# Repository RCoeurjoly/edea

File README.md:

# edea python library

The core python library and command line interface for the EDeA project.

## Documentation
[latest docs](https://edea-dev.gitlab.io/edea/latest/)

## Getting started
[Getting started](https://edea-dev.gitlab.io/edea/latest/get_started.html)

## CHANGELOG
[CHANGELOG](https://edea-dev.gitlab.io/edea/latest/changelog.html)

## Developer documentation
[Developer docs](https://edea-dev.gitlab.io/edea/latest/developer.html)

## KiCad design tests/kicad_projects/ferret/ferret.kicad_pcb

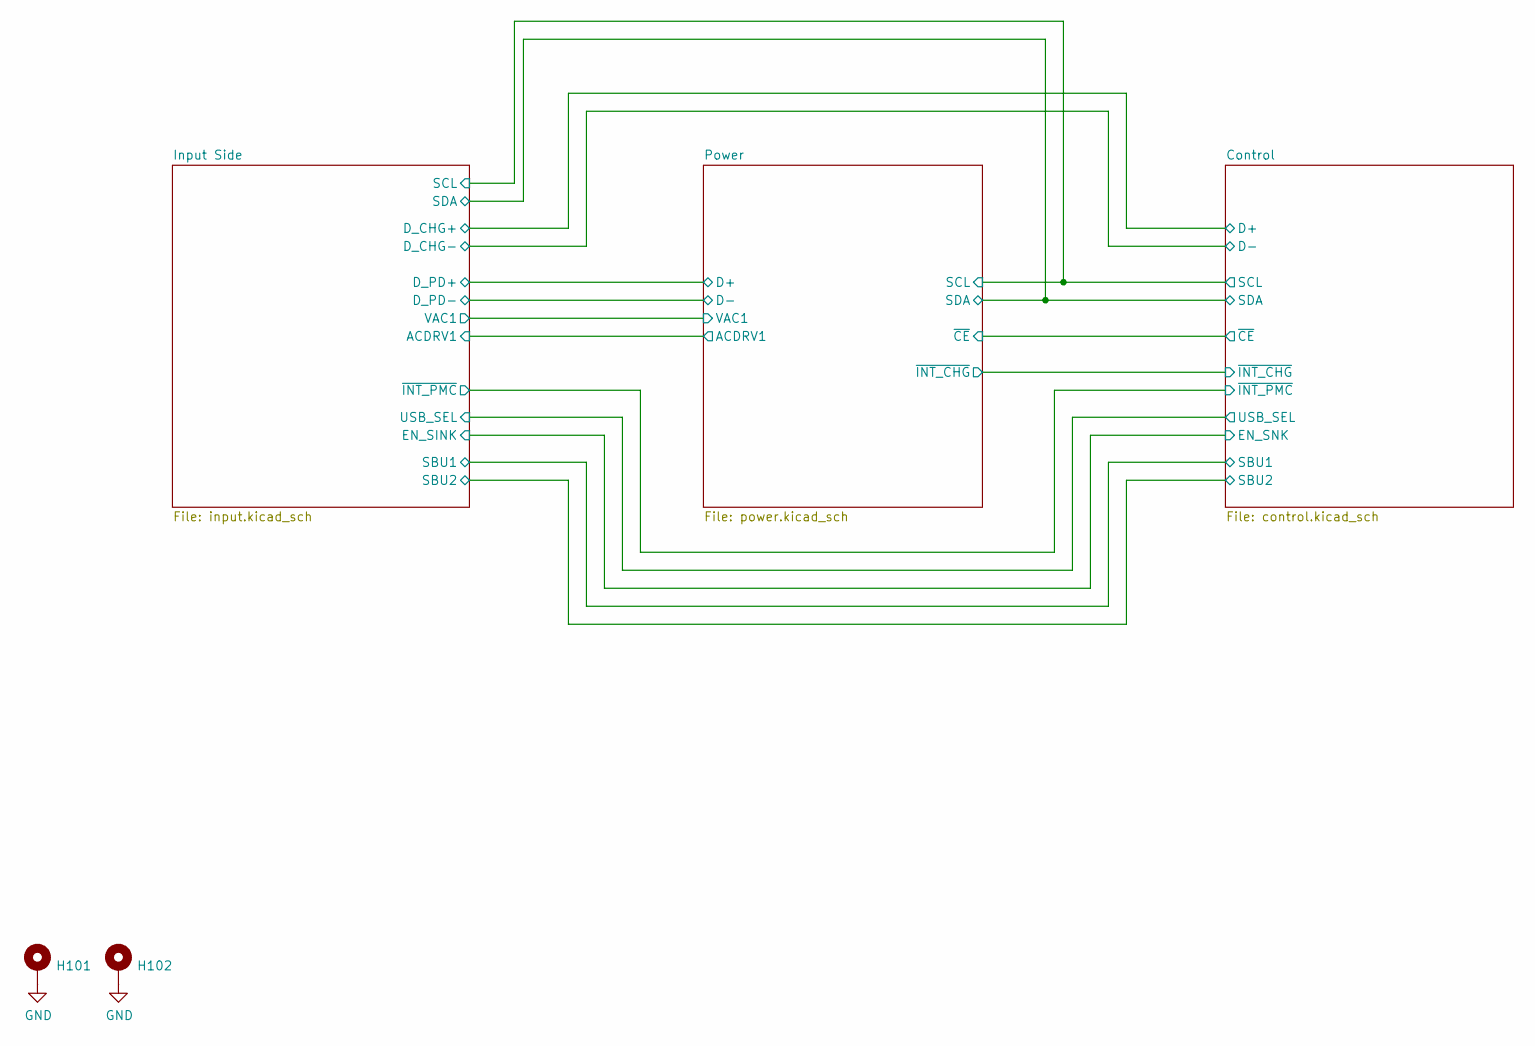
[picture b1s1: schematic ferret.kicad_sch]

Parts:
H101, H102: MountingHole_Pad; MountingHole_3.2mm_M3_ISO14580_Pad; MPN DNP

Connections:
GND: H101.1, H102.1; also elsewhere on the board

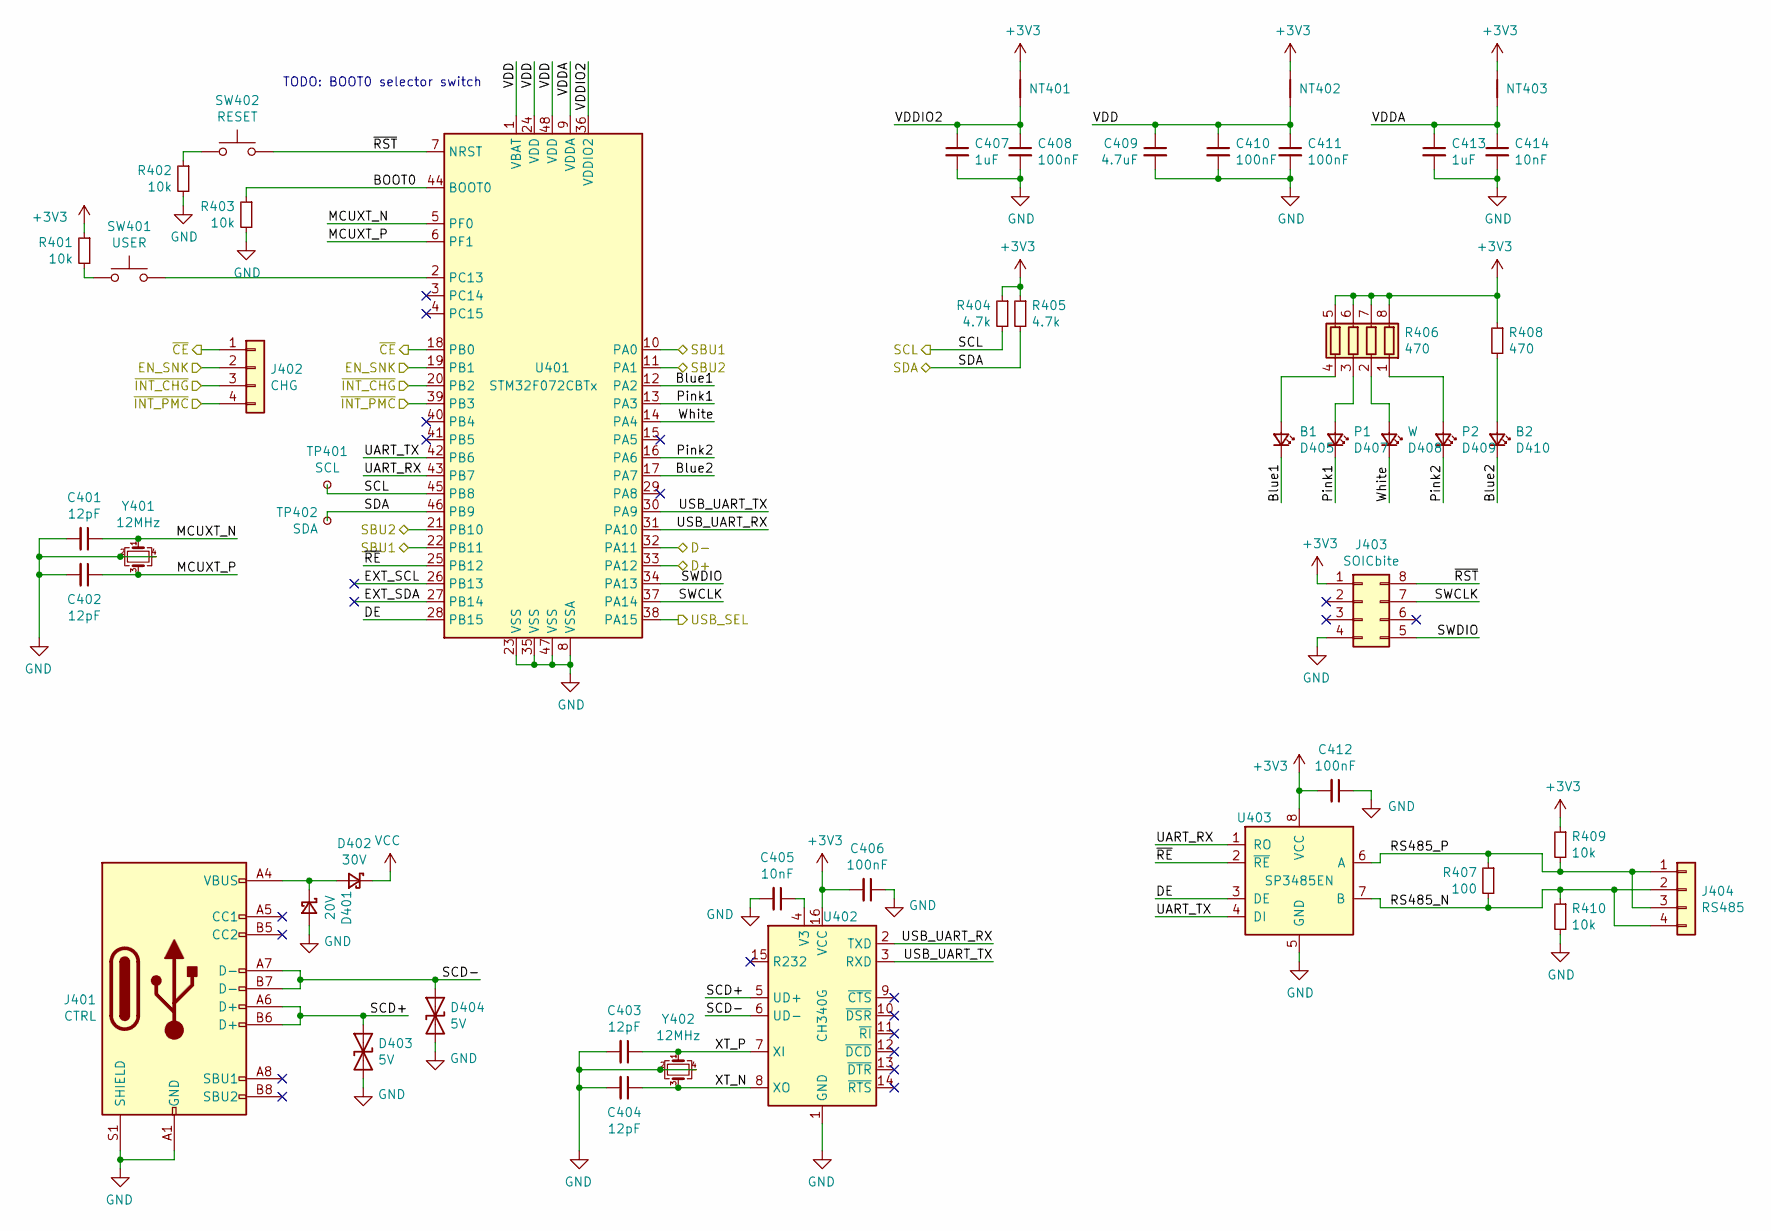
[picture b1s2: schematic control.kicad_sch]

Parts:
C401, C402, C403, C404: 12pF; C_0402_1005Metric; MPN 0402CG120J500NT; LCSC C1547
C405, C414: 10nF; C_0402_1005Metric; LCSC C15195
C406, C408, C410, C411, C412: 100nF; C_0402_1005Metric; MPN CL05B104KO5NNNC; JLC 0402
C407, C413: 1uF; C_0402_1005Metric; LCSC C52923
C409: 4.7uF; C_0603_1608Metric; MPN CL10A475KO8NNNC; JLC 0603
D401: 20V; D_SOD-123; MPN B5819W; LCSC C8598
D402: 30V; D_SOD-123; MPN B5819W; LCSC C8598
D403, D404: 5V; D_SOD-523; MPN ESD5Z3.3T1G; JLC SOD-523
D405: B1; LED_0603_1608Metric_Castellated; MPN OSB60603C1E
D407: P1; LED_0603_1608Metric_Castellated; MPN OSK40603C1E
D408: W; LED_0603_1608Metric_Castellated; MPN OSW50603C1E
D409: P2; LED_0603_1608Metric_Castellated; MPN OSK40603C1E
D410: B2; LED_0603_1608Metric_Castellated; MPN OSB60603C1E
J401: CTRL; USB_C_Receptacle_XKB_U262-16XN-4BVC11
J402: CHG; PinHeader_1x04_P2.54mm_Vertical
J403: SOICbite; SOIC_clipProgSmall
J404: RS485; PinHeader_1x04_P2.54mm_Vertical
NT401: VDDIO2; NetTie-2_SMD_Pad0.5mm; MPN DNP
NT402: VDD; NetTie-2_SMD_Pad0.5mm; MPN DNP
NT403: VDDA; NetTie-2_SMD_Pad0.5mm; MPN DNP
R401, R402, R403, R409, R410: 10k; R_0603_1608Metric; JLC 0603
R404, R405: 4.7k; R_0603_1608Metric; JLC 0603
R406: 470; R_Array_Convex_4x0603; MPN 4D03WGJ0471T5E; JLC 0603_x4
R407: 100; R_0603_1608Metric; MPN 0603WAF1000T5E; JLC 0603
R408: 470; R_0603_1608Metric; JLC 0603
SW401: USER; SW_SPST_PTS636_G
SW402: RESET; SW_SPST_PTS636_G
TP401: SCL; TestPoint_THTPad_D2.0mm_Drill1.0mm
TP402: SDA; TestPoint_THTPad_D2.0mm_Drill1.0mm
U401: STM32F072CBTx; LQFP-48_7x7mm_P0.5mm; MPN STM32F072C8T6; JLC LQFP-48_7.0x7.0x0.5P
U402: CH340G; SOIC-16_3.9x9.9mm_P1.27mm; MPN CH340G; JLC SOIC-16_3.9x9.9x1.27P
U403: SP3485EN; SOIC-8_3.9x4.9mm_P1.27mm; MPN SP3485EN-L/TR; JLC SOIC-8_3.9x4.9x1.27P
Y401, Y402: 12MHz; Crystal_SMD_3225-4Pin_3.2x2.5mm; MPN X322512MSB4SI; JLC SMD-3225_4P

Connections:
+3V3: C406.2, C412.2, J403.1, NT401.1, NT402.1, NT403.1, R401.1, R404.1, R405.1, R406.5 (R4.2), R406.6 (R3.2), R406.7 (R2.2), R406.8 (R1.2), R408.1, R409.1, U402.16 (VCC), U403.8 (VCC); also elsewhere on the board
/Control/BOOT0: R403.1, U401.44 (BOOT0)
/Control/Blue1: D405.1 (K), U401.12 (PA2)
/Control/Blue2: D410.1 (K), U401.17 (PA7)
/Control/D+: U401.33 (PA12); also elsewhere on the board
/Control/D-: U401.32 (PA11); also elsewhere on the board
/Control/DE: U401.28 (PB15), U403.3 (DE)
/Control/EXT_SCL: U401.26 (PB13)
/Control/EXT_SDA: U401.27 (PB14)
/Control/MCUXT_N: C401.1, U401.5 (PF0), Y401.1
/Control/MCUXT_P: C402.1, U401.6 (PF1), Y401.3
/Control/Pink1: D407.1 (K), U401.13 (PA3)
/Control/Pink2: D409.1 (K), U401.16 (PA6)
/Control/RS485_N: J404.2, J404.4, R407.2, R410.1, U403.7 (B)
/Control/RS485_P: J404.1, J404.3, R407.1, R409.2, U403.6 (A)
/Control/SBU1: U401.10 (PA0), U401.22 (PB11); also elsewhere on the board
/Control/SBU2: U401.11 (PA1), U401.21 (PB10); also elsewhere on the board
/Control/SCD+: D403.1 (A1), J401.A6 (D+), J401.B6 (D+), U402.5 (UD+)
/Control/SCD-: D404.1 (A1), J401.A7 (D-), J401.B7 (D-), U402.6 (UD-)
/Control/SCL: R404.2, TP401.1, U401.45 (PB8); also elsewhere on the board
/Control/SDA: R405.2, TP402.1, U401.46 (PB9); also elsewhere on the board
/Control/SWCLK: J403.7, U401.37 (PA14)
/Control/SWDIO: J403.5, U401.34 (PA13)
/Control/UART_RX: U401.43 (PB7), U403.1 (RO)
/Control/UART_TX: U401.42 (PB6), U403.4 (DI)
/Control/USB_SEL: U401.38 (PA15); also elsewhere on the board
/Control/USB_UART_RX: U401.31 (PA10), U402.2 (TXD)
/Control/USB_UART_TX: U401.30 (PA9), U402.3 (RXD)
/Control/VDD: C409.1, C410.1, C411.1, NT402.2, U401.1 (VBAT), U401.24 (VDD), U401.48 (VDD)
/Control/VDDA: C413.1, C414.1, NT403.2, U401.9 (VDDA)
/Control/VDDIO2: C407.1, C408.1, NT401.2, U401.36 (VDDIO2)
/Control/White: D408.1 (K), U401.14 (PA4)
/Control/XT_N: C404.1, U402.8 (XO), Y402.3
/Control/XT_P: C403.1, U402.7 (XI), Y402.1
/Control/~CE: J402.1, U401.18 (PB0); also elsewhere on the board
/Control/~INT_CHG: J402.3, U401.20 (PB2); also elsewhere on the board
/Control/~INT_PMC: J402.4, U401.39 (PB3); also elsewhere on the board
/Control/~RE: U401.25 (PB12), U403.2 (~RE)
/Control/~RST: J403.8, SW402.2, U401.7 (NRST)
/Input Side/EN_SINK: J402.2, U401.19 (PB1); also elsewhere on the board
GND: C401.2, C402.2, C403.2, C404.2, C405.2, C406.1, C407.2, C408.2, C409.2, C410.2, C411.2, C412.1, C413.2, C414.2, D401.2 (A), D403.2 (A2), D404.2 (A2), J401.A1 (GND), J401.A12 (GND), J401.B1 (GND), J401.B12 (GND), J401.S1 (SHIELD), J403.4, R402.2, R403.2, R410.2, U401.8 (VSSA), U401.23 (VSS), U401.35 (VSS), U401.47 (VSS), U402.1 (GND), U403.5 (GND), Y401.2, Y401.4, Y402.2, Y402.4; also elsewhere on the board
unnamed: C405.1, U402.4 (V3)
unnamed: D401.1 (K), D402.2 (A), J401.A4 (VBUS), J401.A9 (VBUS), J401.B4 (VBUS), J401.B9 (VBUS)
unnamed: D405.2 (A), R406.4 (R4.1)
unnamed: D407.2 (A), R406.3 (R3.1)
unnamed: D408.2 (A), R406.2 (R2.1)
unnamed: D409.2 (A), R406.1 (R1.1)
unnamed: D410.2 (A), R408.2
unnamed: R401.2, SW401.1
unnamed: R402.1, SW402.1
unnamed: SW401.2, U401.2 (PC13)
VCC: D402.1 (K); also elsewhere on the board

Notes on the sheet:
TODO: BOOT0 selector switch

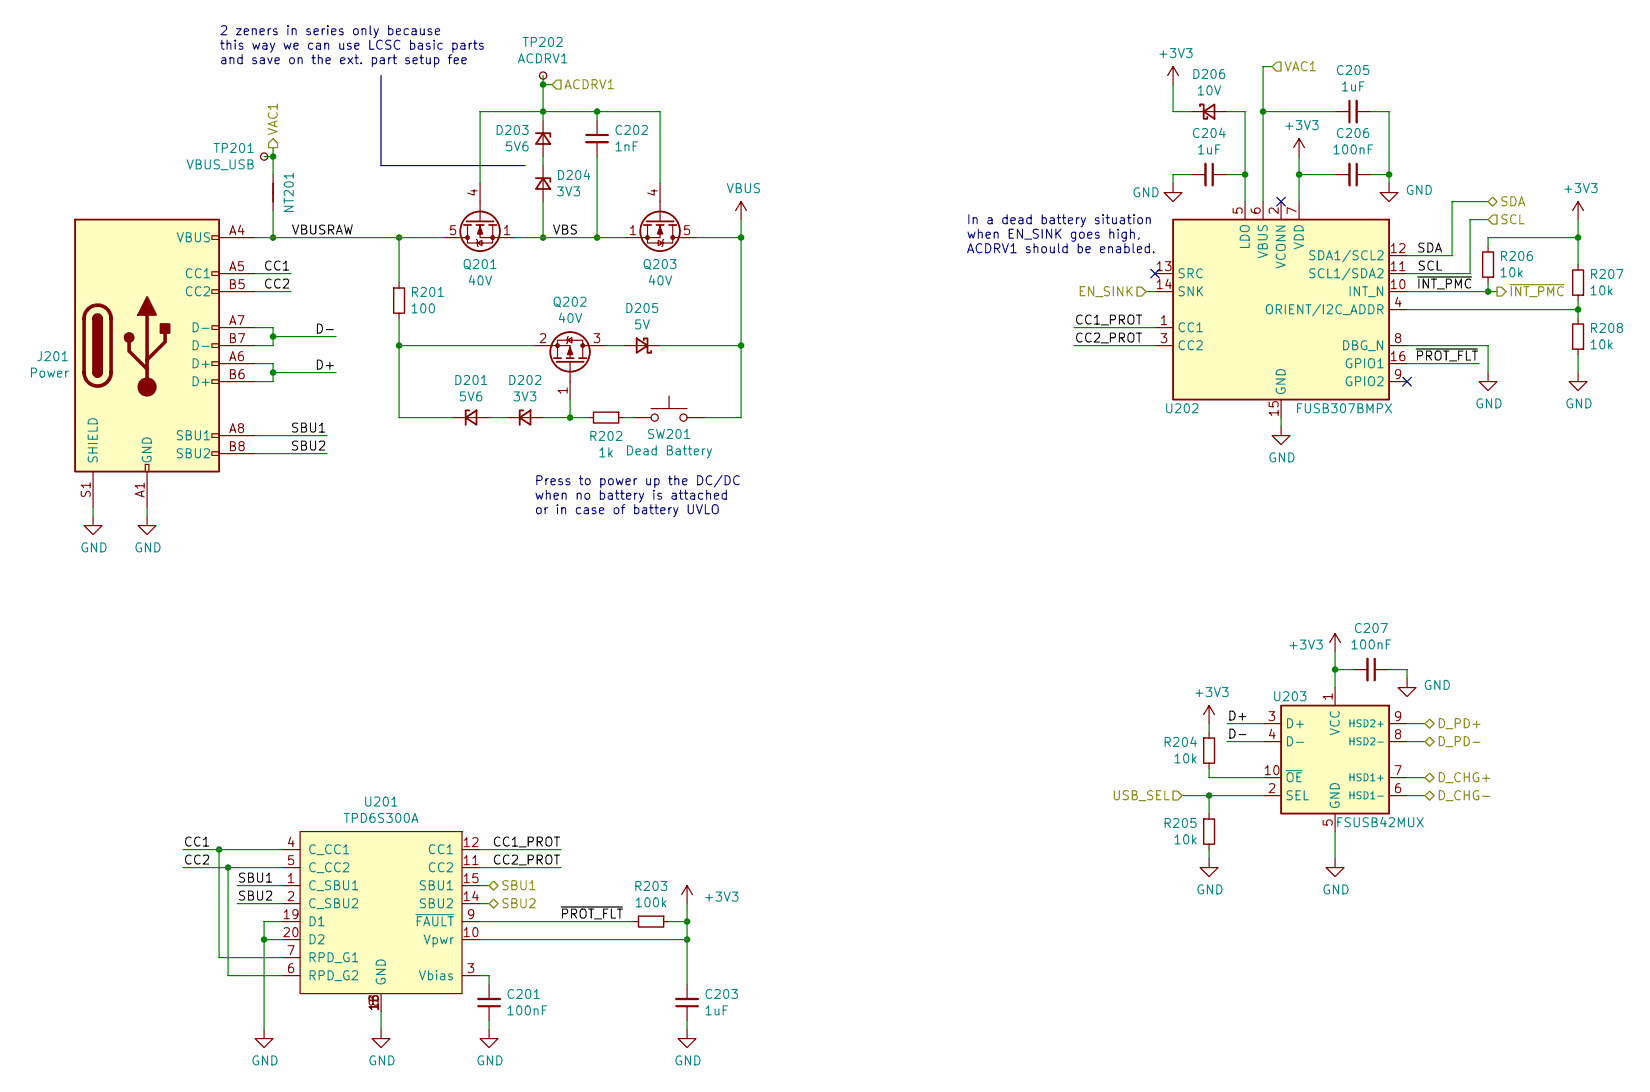
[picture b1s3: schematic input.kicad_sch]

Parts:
C201, C206: 100nF; C_0603_1608Metric; MPN CC0603KRX7R9BB104; JLC 0603
C202: 1nF; C_0402_1005Metric; JLC 0402
C203: 1uF; C_0603_1608Metric; MPN CL10A105KB8NNNC; LCSC C15849
C204: 1uF; C_0603_1608Metric
C205: 1uF; C_0603_1608Metric; LCSC C15849
C207: 100nF; C_0402_1005Metric; JLC 0402
D201, D203: 5V6; D_MiniMELF; MPN ZMM5V6; JLC LL-34
D202, D204: 3V3; D_MiniMELF; MPN ZMM3V3; JLC LL-34
D205: 5V; D_SOD-123; MPN B5819W; JLC SOD-123
D206: 10V; D_SOD-123; MPN B5819W; LCSC C8598
J201: Power; USB_C_Receptacle_XKB_U262-16XN-4BVC11
NT201: UwU; NetTie-2_SMD_Pad0.5mm; MPN DNP
Q201, Q203: 40V; Vishay_PowerPAK_1212-8_Single; MPN SiSS10ADN
Q202: 40V; SOT-23; MPN AO3401; JLC SOT-23-3L
R201: 100; R_1206_3216Metric; MPN 1206W4F1000T5E; JLC 1206
R202: 1k; R_0603_1608Metric; MPN 0603WAF1001T5E; JLC 0603
R203: 100k; R_0402_1005Metric; JLC 0402
R204, R205: 10k; R_0603_1608Metric; JLC 0603
R206: 10k; R_0402_1005Metric; JLC 0402
R207, R208: 10k; R_0603_1608Metric; MPN DNP; JLC 0603
SW201: Dead Battery; SW_SPST_PTS636_G
TP201: VBUS_USB; TestPoint_THTPad_D2.0mm_Drill1.0mm
TP202: ACDRV1; TestPoint_THTPad_D2.0mm_Drill1.0mm
U201: TPD6S300A; QFN-20-1EP_3x3mm_P0.4mm_EP1.65x1.65mm; MPN TPD6S300ARUKR
U202: FUSB307BMPX; WQFN-16-1EP_3x3mm_P0.5mm_EP1.75x1.75mm
U203: FSUSB42MUX; MSOP-10_3x3mm_P0.5mm; MPN FSUSB42MUX; JLC MSOP-10_3.0x3.0x0.5P

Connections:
+3V3: C203.2, C206.2, C207.2, D206.1 (K), R203.1, R204.1, R206.2, R207.2, U201.10 (Vpwr), U202.7 (VDD), U203.1 (VCC); also elsewhere on the board
/Control/D+: U203.7 (HSD1+); also elsewhere on the board
/Control/D-: U203.6 (HSD1-); also elsewhere on the board
/Control/SBU1: J201.A8 (SBU1), U201.1 (C_SBU1), U201.15 (SBU1); also elsewhere on the board
/Control/SBU2: J201.B8 (SBU2), U201.2 (C_SBU2), U201.14 (SBU2); also elsewhere on the board
/Control/SCL: U202.11 (SCL1/SDA2); also elsewhere on the board
/Control/SDA: U202.12 (SDA1/SCL2); also elsewhere on the board
/Control/USB_SEL: R205.1, U203.2 (SEL); also elsewhere on the board
/Control/~INT_PMC: R206.1, U202.10 (INT_N); also elsewhere on the board
/Input Side/ACDRV1: C202.1, D203.1 (K), Q201.4 (G), Q203.4 (G), TP202.1; also elsewhere on the board
/Input Side/CC1: J201.A5 (CC1), U201.4 (C_CC1), U201.7 (RPD_G1)
/Input Side/CC1_PROT: U201.12 (CC1), U202.1 (CC1)
/Input Side/CC2: J201.B5 (CC2), U201.5 (C_CC2), U201.6 (RPD_G2)
/Input Side/CC2_PROT: U201.11 (CC2), U202.3 (CC2)
/Input Side/D+: J201.A6 (D+), J201.B6 (D+), U203.3 (D+)
/Input Side/D-: J201.A7 (D-), J201.B7 (D-), U203.4 (D-)
/Input Side/EN_SINK: U202.14 (SNK); also elsewhere on the board
/Input Side/VAC1: C205.1, NT201.1, TP201.1, U202.6 (VBUS); also elsewhere on the board
/Input Side/VBS: C202.2, D204.2 (A), Q201.1 (S), Q201.2 (S), Q201.3 (S), Q203.1 (S), Q203.2 (S), Q203.3 (S)
/Input Side/VBUSRAW: J201.A4 (VBUS), J201.A9 (VBUS), J201.B4 (VBUS), J201.B9 (VBUS), NT201.2, Q201.5 (D), R201.1
/Input Side/~PROT_FLT: R203.2, U201.9 (~FAULT), U202.16 (GPIO1)
/Power/D+: U203.9 (HSD2+); also elsewhere on the board
/Power/D-: U203.8 (HSD2-); also elsewhere on the board
GND: C201.1, C203.1, C204.2, C205.2, C206.1, C207.1, J201.A1 (GND), J201.A12 (GND), J201.B1 (GND), J201.B12 (GND), J201.S1 (SHIELD), R205.2, R208.1, U201.8 (GND), U201.13 (GND), U201.16 (NC), U201.17 (NC), U201.18 (GND), U201.19 (D1), U201.20 (D2), U201.21 (Thermal_Pad), U202.8 (DBG_N), U202.15 (GND), U202.17 (GND), U203.5 (GND); also elsewhere on the board
unnamed: C201.2, U201.3 (Vbias)
unnamed: C204.1, D206.2 (A), U202.5 (LDO)
unnamed: D201.1 (K), Q202.2 (S), R201.2
unnamed: D201.2 (A), D202.1 (K)
unnamed: D202.2 (A), Q202.1 (G), R202.2
unnamed: D203.2 (A), D204.1 (K)
unnamed: D205.2 (A), Q202.3 (D)
unnamed: R202.1, SW201.1
unnamed: R204.2, U203.10 (~OE)
unnamed: R207.1, R208.2, U202.4 (ORIENT/I2C_ADDR)
VBUS: D205.1 (K), Q203.5 (D), SW201.2; also elsewhere on the board

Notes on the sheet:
2 zeners in series only because this way we can use LCSC basic parts and save on the ext. part setup fee
In a dead battery situation when EN_SINK goes high, ACDRV1 should be enabled.
Press to power up the DC/DC when no battery is attached or in case of battery UVLO

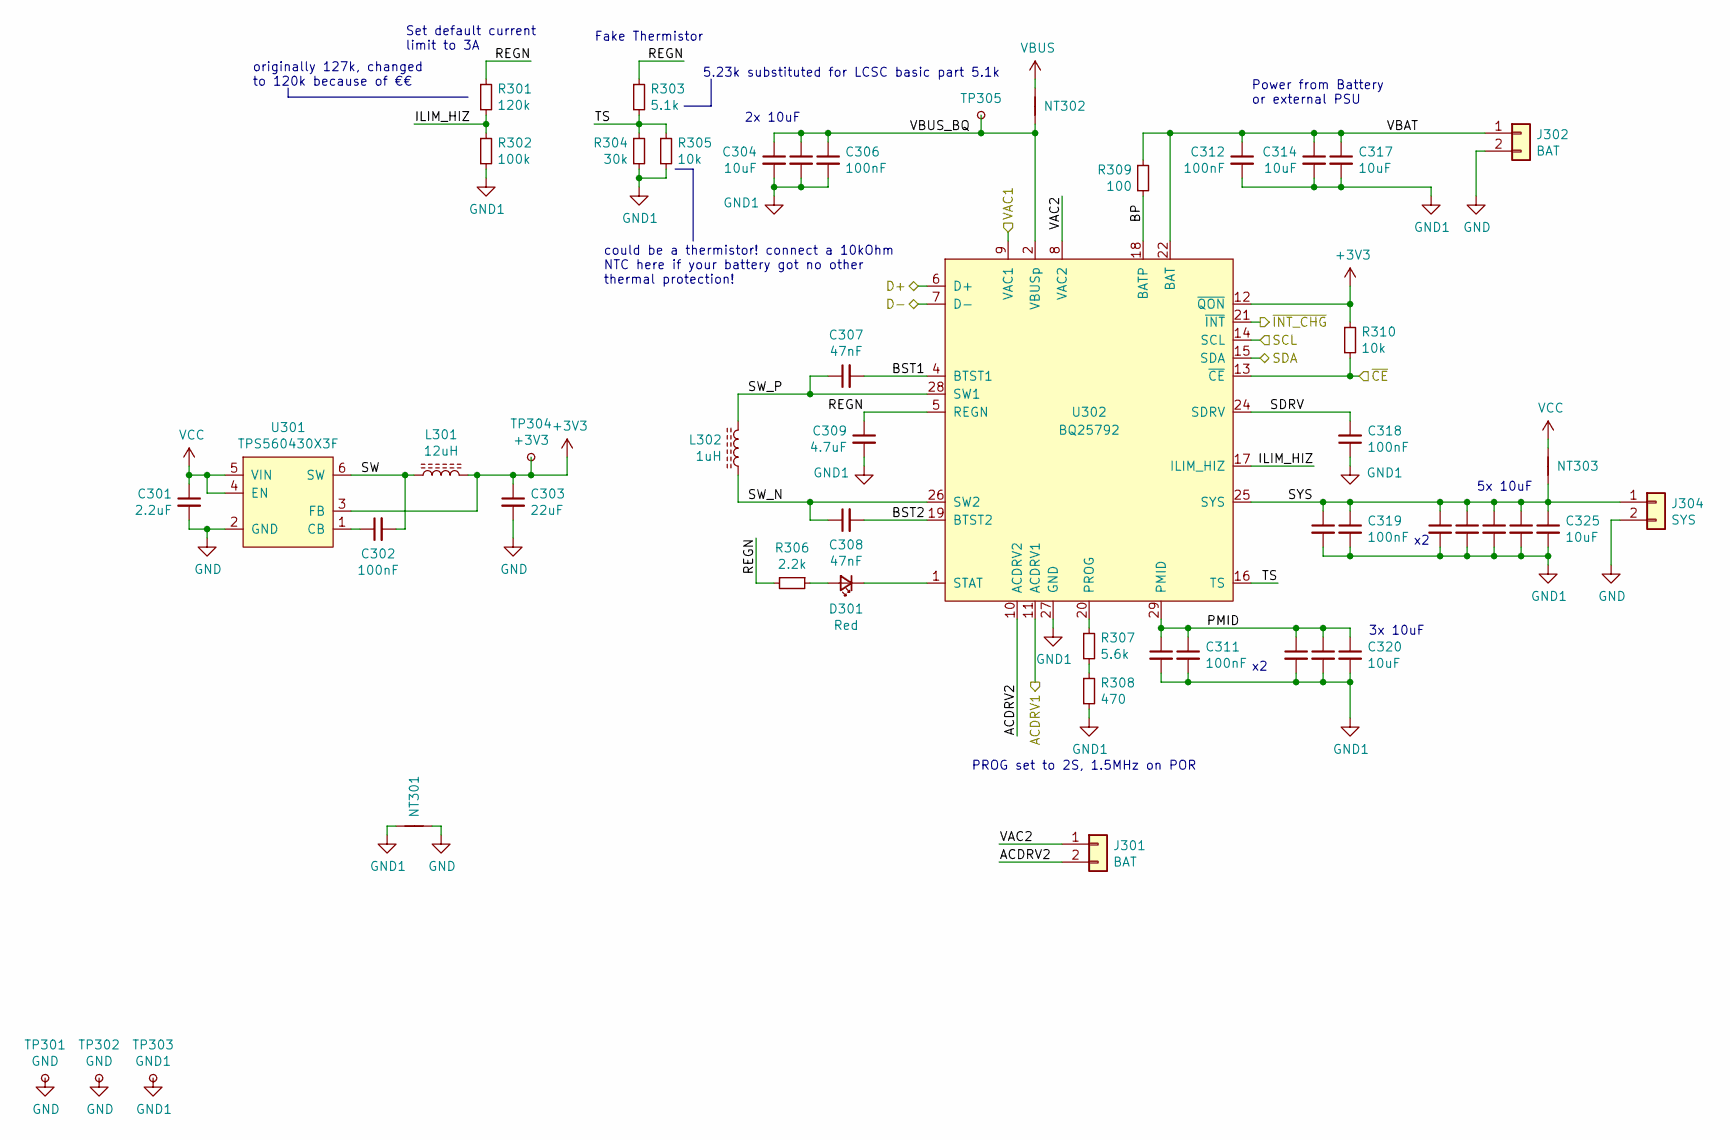
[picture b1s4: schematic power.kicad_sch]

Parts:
C301: 2.2uF; C_0805_2012Metric; MPN 0805F225M500NT; JLC 0805
C302: 100nF; C_0603_1608Metric; MPN CC0603KRX7R9BB104; JLC 0603
C303: 22uF; C_0805_2012Metric; MPN CL21A226MAQNNNE; JLC 0805
C304, C305, C313, C314, C316, C317, C320, C321, C322, C323, C324, C325: 10uF; C_1206_3216Metric; MPN CL31A106KBHNNNE; JLC 1206
C306, C312: 100nF; C_0402_1005Metric; JLC 0402
C307, C308: 47nF; C_0603_1608Metric
C309: 4.7uF; C_0603_1608Metric; MPN CL10A475KO8NNNC; JLC 0603
C310, C311, C315, C319: 100nF; C_0603_1608Metric
C318: 100nF; C_0402_1005Metric
D301: Red; LED_0603_1608Metric_Castellated
J301, J302: BAT; PinSocket_1x02_P2.54mm_Vertical
J304: SYS; PinSocket_1x02_P2.54mm_Vertical
L301: 12uH; L_Bourns_SRN6045TA; MPN SRN6045TA-120M
L302: 1uH; L_Bourns_SRP1245A; MPN SRP1265A-1R0M
NT301: chonk; NetTie-2_SMD_Pad2.0mm
NT302: chonk_vbus; NetTie-2_SMD_Pad2.0mm
NT303: chonk; NetTie-2_SMD_Pad0.5mm
R301: 120k; R_0603_1608Metric; JLC 0603
R302: 100k; R_0603_1608Metric; JLC 0603
R303: 5.1k; R_0603_1608Metric; JLC 0603
R304: 30k; R_0603_1608Metric; LCSC C22984
R305, R310: 10k; R_0603_1608Metric; JLC 0603
R306: 2.2k; R_0603_1608Metric; MPN 0603WAF2201T5E; JLC 0603
R307: 5.6k; R_0402_1005Metric; JLC 0603
R308: 470; R_0402_1005Metric; LCSC C25117
R309: 100; R_0603_1608Metric; MPN 0603WAF1000T5E; JLC 0603
TP301, TP302: GND; TestPoint_THTPad_D2.0mm_Drill1.0mm
TP303: GND1; TestPoint_THTPad_D2.0mm_Drill1.0mm
TP304: +3V3; TestPoint_THTPad_D2.0mm_Drill1.0mm
TP305: VBUS_BQ; TestPoint_THTPad_D2.0mm_Drill1.0mm
U301: TPS560430X3F; SOT-23-6; JLC SOT-23-6L
U302: BQ25792; Texas_VQFN-HR_RQM_4x4mm_P0.40-0.45mm

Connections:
+3V3: C303.1, L301.2, R310.1, TP304.1, U301.3 (FB), U302.12 (~QON); also elsewhere on the board
/Control/SCL: U302.14 (SCL); also elsewhere on the board
/Control/SDA: U302.15 (SDA); also elsewhere on the board
/Control/~CE: R310.2, U302.13 (~CE); also elsewhere on the board
/Control/~INT_CHG: U302.21 (~INT); also elsewhere on the board
/Input Side/ACDRV1: U302.11 (ACDRV1); also elsewhere on the board
/Input Side/VAC1: U302.9 (VAC1); also elsewhere on the board
/Power/ACDRV2: J301.2, U302.10 (ACDRV2)
/Power/BP: R309.2, U302.18 (BATP)
/Power/BST1: C307.2, U302.4 (BTST1)
/Power/BST2: C308.2, U302.19 (BTST2)
/Power/D+: U302.6 (D+); also elsewhere on the board
/Power/D-: U302.7 (D-); also elsewhere on the board
/Power/ILIM_HIZ: R301.2, R302.1, U302.17 (ILIM_HIZ)
/Power/PMID: C310.1, C311.1, C313.1, C316.1, C320.1, U302.29 (PMID)
/Power/REGN: C309.1, R301.1, R303.1, R306.2, U302.5 (REGN)
/Power/SDRV: C318.2, U302.24 (SDRV)
/Power/SW: C302.2, L301.1, U301.6 (SW)
/Power/SW_N: C308.1, L302.1, U302.26 (SW2)
/Power/SW_P: C307.1, L302.2, U302.28 (SW1)
/Power/SYS: C315.1, C319.1, C321.1, C322.1, C323.1, C324.1, C325.1, J304.1, NT303.2, U302.25 (SYS)
/Power/TS: R303.2, R304.1, R305.1, U302.16 (TS)
/Power/VAC2: J301.1, U302.8 (VAC2)
/Power/VBAT: C312.1, C314.1, C317.1, J302.1, R309.1, U302.22 (BAT), U302.23 (BAT)
GND: C301.2, C303.2, J302.2, J304.2, NT301.2, TP301.1, TP302.1, U301.2 (GND); also elsewhere on the board
GND1: C304.2, C305.2, C306.2, C309.2, C310.2, C311.2, C312.2, C313.2, C314.2, C315.2, C316.2, C317.2, C318.1, C319.2, C320.2, C321.2, C322.2, C323.2, C324.2, C325.2, NT301.1, R302.2, R304.2, R305.2, R308.2, TP303.1, U302.27 (GND)
unnamed: C302.1, U301.1 (CB)
unnamed: D301.1 (K), U302.1 (STAT)
unnamed: D301.2 (A), R306.1
unnamed: R307.1, U302.20 (PROG)
unnamed: R307.2, R308.1
VBUS: NT302.1; also elsewhere on the board
VBUSp: C304.1, C305.1, C306.1, NT302.2, TP305.1, U302.2 (VBUSp), U302.3 (VBUSp)
VCC: C301.1, NT303.1, U301.4 (EN), U301.5 (VIN); also elsewhere on the board

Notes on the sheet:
could be a thermistor! connect a 10kOhm NTC here if your battery got no other thermal protection!
2x 10uF
PROG set to 2S, 1.5MHz on POR
originally 127k, changed to 120k because of €€
5x 10uF
Power from Battery or external PSU
Set default current limit to 3A
5.23k substituted for LCSC basic part 5.1k
Fake Thermistor
3x 10uF

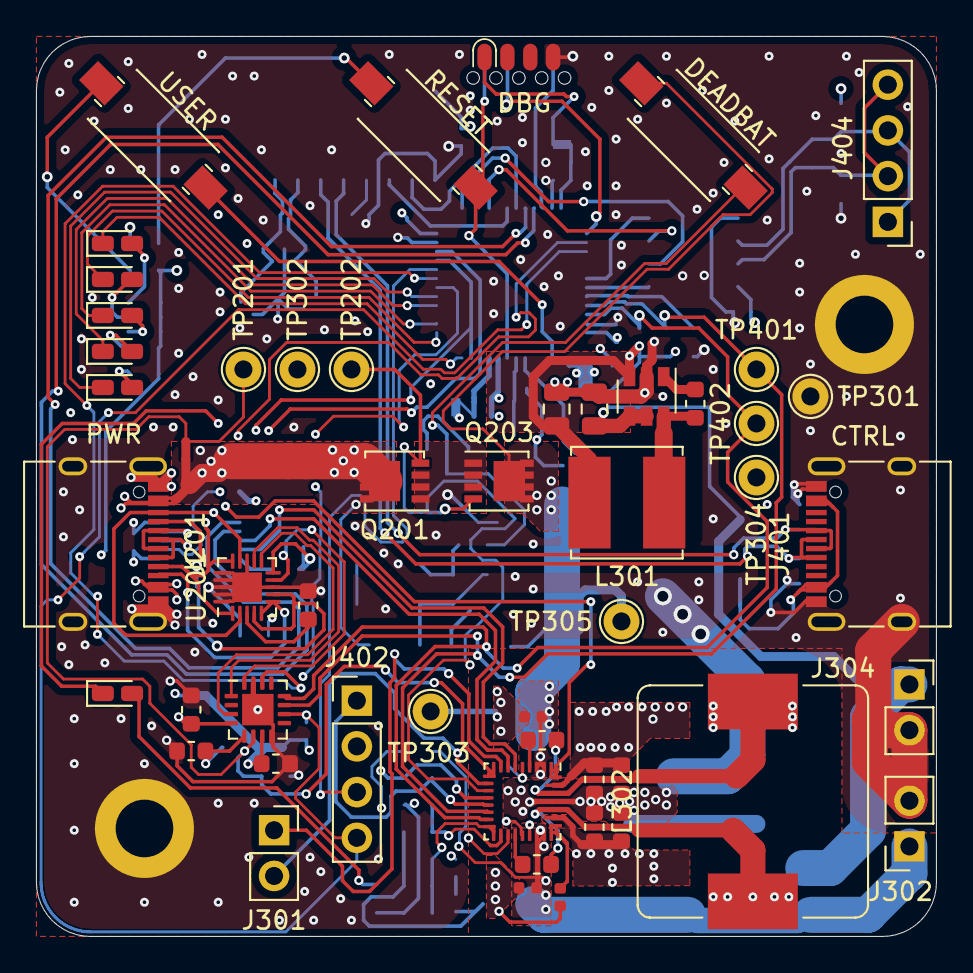
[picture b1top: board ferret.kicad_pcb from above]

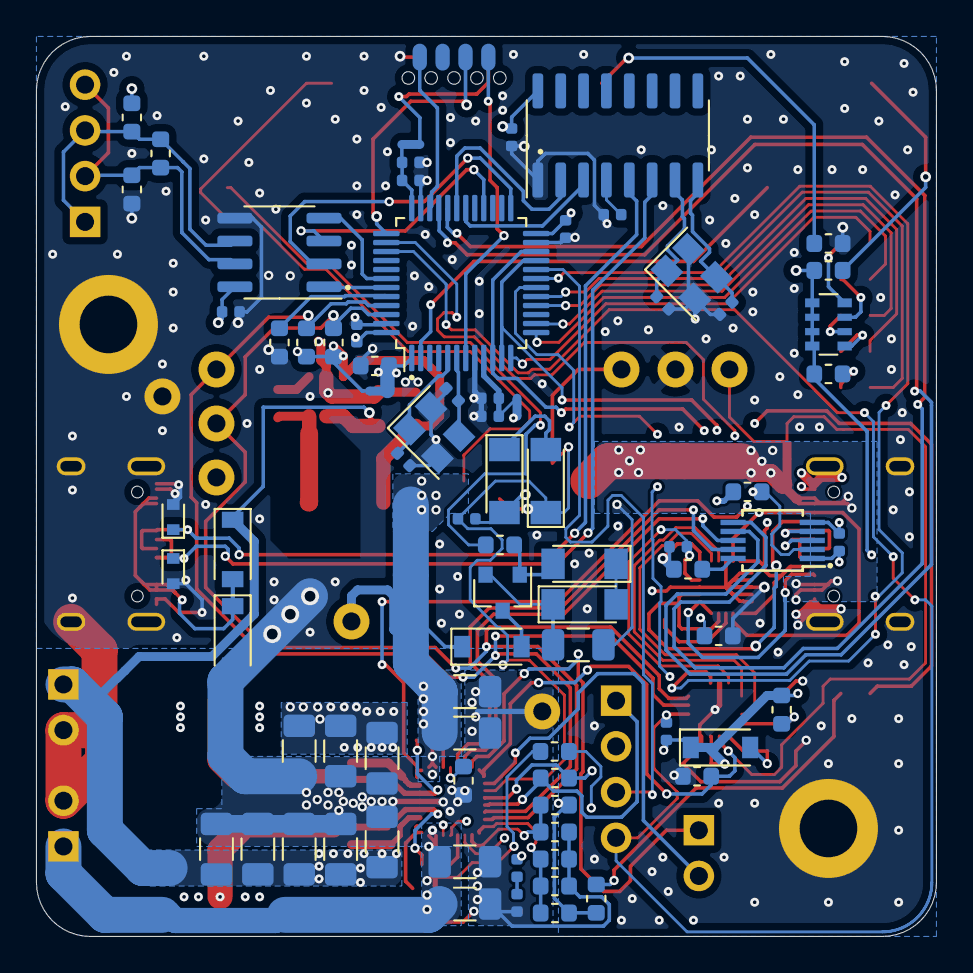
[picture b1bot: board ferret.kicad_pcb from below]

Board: 4 copper layers, 50.0 x 50.0 mm, 134 parts (81 on the bottom side), 96 nets.

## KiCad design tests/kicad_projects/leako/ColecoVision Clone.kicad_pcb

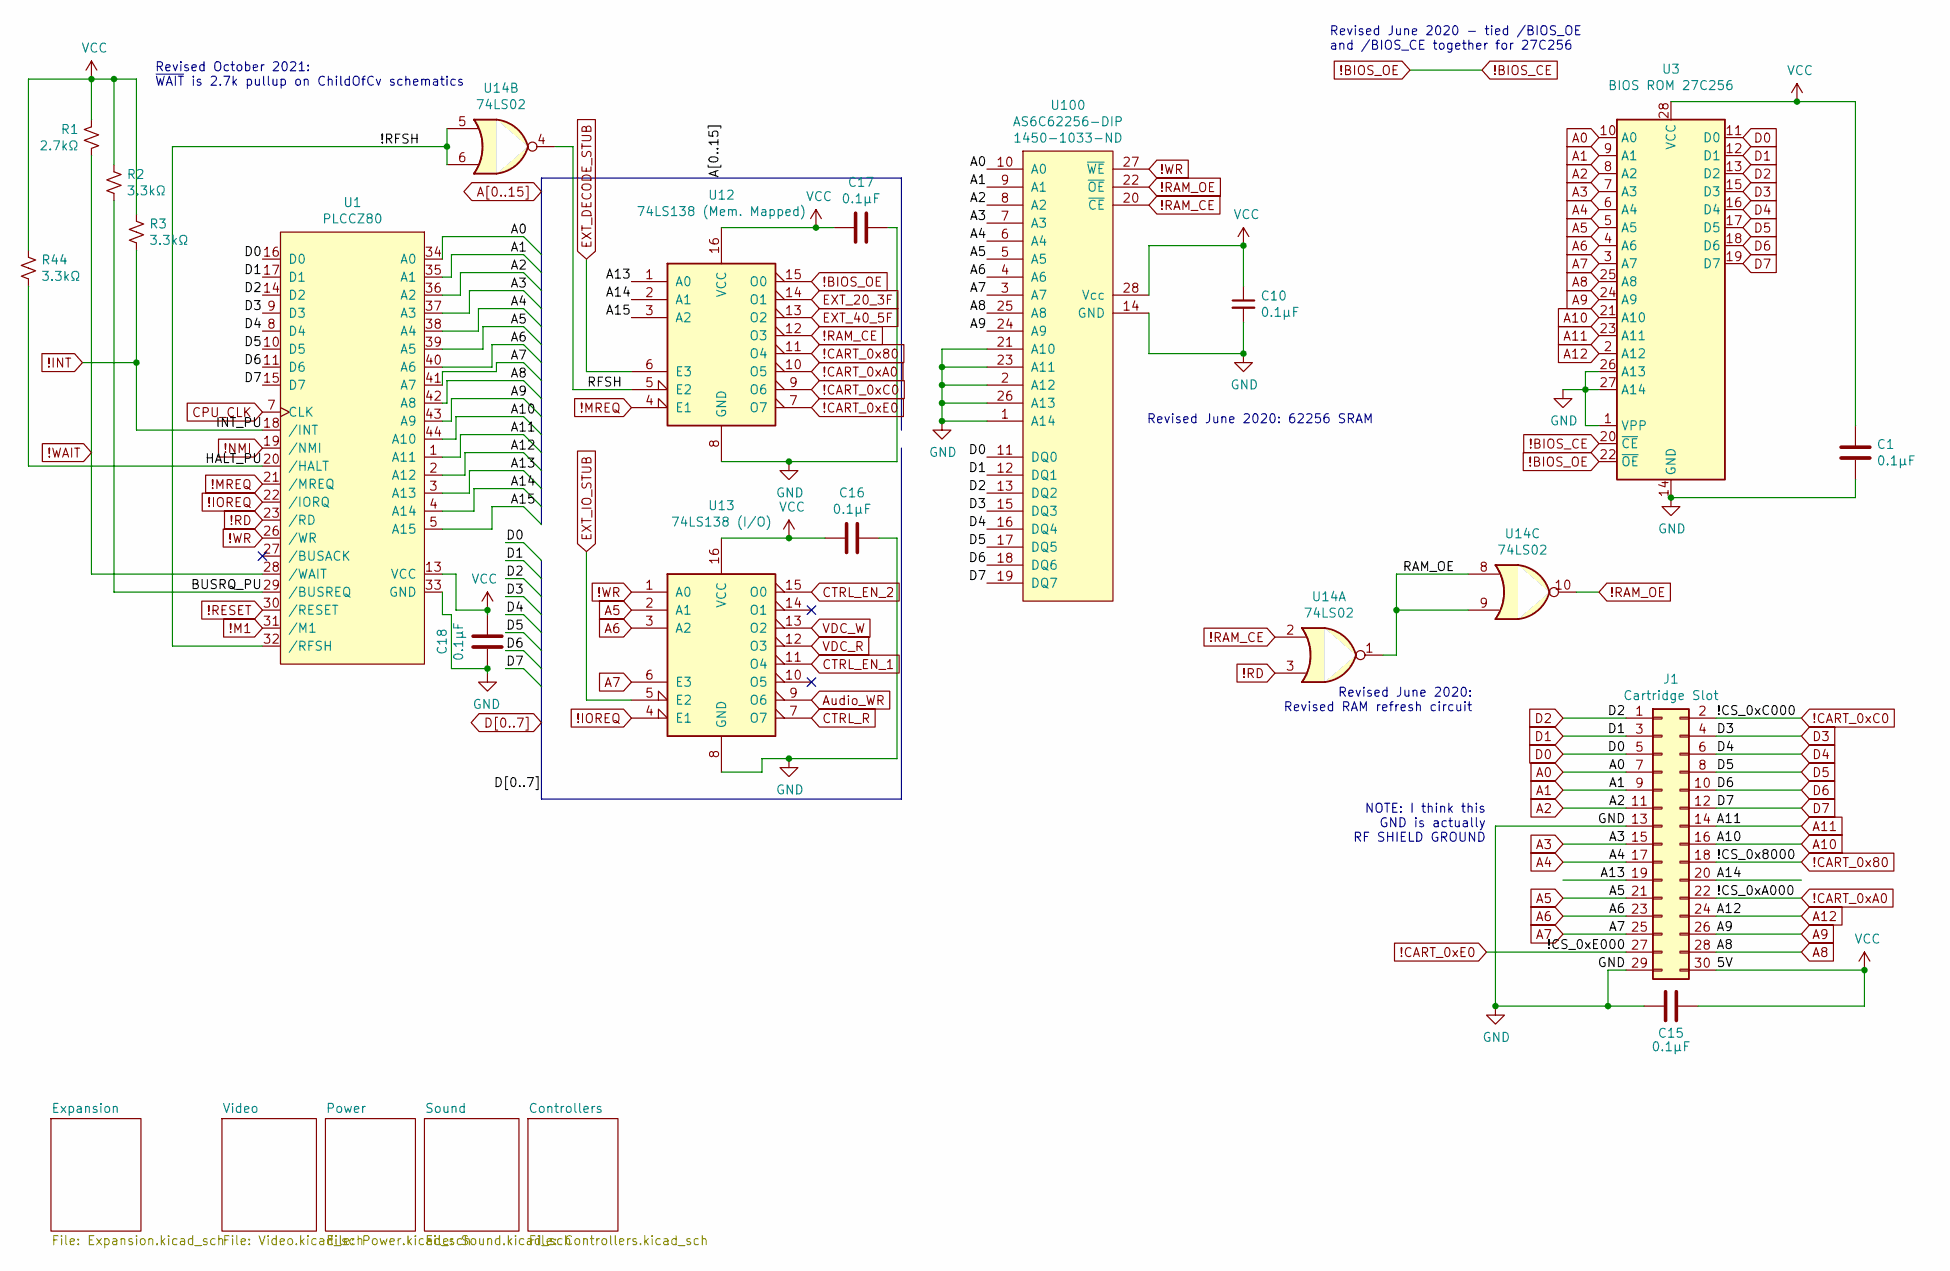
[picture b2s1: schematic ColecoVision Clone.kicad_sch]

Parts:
C1, C10, C15, C16, C17, C18: 0.1µF; C_0805_HandSoldering; DigiKey 1276-1099-1-ND
J1: Cartridge Slot; Sullins_Cart_Slot; DigiKey A31715-ND
R1: 2.7kΩ; R_0805_HandSoldering; DigiKey RMCF0805JT2K70CT-ND
R2, R3, R44: 3.3kΩ; R_0805_HandSoldering; DigiKey RMCF0805JT3K30CT-ND
U1: PLCCZ80; PLCC44; DigiKey 2057-PLCC-44-AT-ND; 269-3899-ND
U3: BIOS ROM 27C256; DIP-28_W15.24mm_Socket_LongPads; DigiKey 2057-ICS-628-T-ND
U12: 74LS138 (Mem. Mapped); SOIC-16_3.9x9.9mm_Pitch1.27mm; DigiKey 296-14883-2-ND
U13: 74LS138 (I/O); SOIC-16_3.9x9.9mm_Pitch1.27mm; DigiKey 296-14883-2-ND
U14: 74LS02; SOIC-14_3.9x8.7mm_Pitch1.27mm; DigiKey 296-14874-1-ND
U100: AS6C62256-DIP; DIP-28_W15.24mm_Socket_LongPads; DigiKey 1450-1033-ND

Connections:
!BIOS_CE: U3.20 (~CE), U3.22 (~OE), U12.15 (O0)
!CART_0x80: J1.18, U12.11 (O4)
!CART_0xA0: J1.22, U12.10 (O5)
!CART_0xC0: J1.2, U12.9 (O6)
!CART_0xE0: J1.27, U12.7 (O7)
!INT: R3.2, U1.18 (/INT); also elsewhere on the board
!IOREQ: U1.22 (/IORQ), U13.4 (E1)
!M1: U1.31 (/M1); also elsewhere on the board
!MREQ: U1.21 (/MREQ), U12.4 (E1)
!NMI: U1.19 (/NMI); also elsewhere on the board
!RAM_CE: U12.12 (O3), U14.2, U100.20 (~CE)
!RAM_OE: U14.10, U100.22 (~OE)
!RD: U1.23 (/RD), U14.3
!RESET: U1.30 (/RESET); also elsewhere on the board
!WAIT: R1.2, U1.28 (/WAIT); also elsewhere on the board
!WR: U1.26 (/WR), U13.1 (A0), U100.27 (~WE)
/!RFSH: U1.32 (/RFSH), U14.5, U14.6
/BUSRQ_PU: R2.2, U1.29 (/BUSREQ)
/HALT_PU: R44.2, U1.20 (/HALT)
/RAM_OE: U14.1, U14.8, U14.9
/RFSH: U12.5 (E2), U14.4
A0: J1.7, U1.34 (A0), U3.10 (A0), U100.10 (A0); also elsewhere on the board
A1: J1.9, U1.35 (A1), U3.9 (A1), U100.9 (A1); also elsewhere on the board
A2: J1.11, U1.36 (A2), U3.8 (A2), U100.8 (A2)
A3: J1.15, U1.37 (A3), U3.7 (A3), U100.7 (A3)
A4: J1.17, U1.38 (A4), U3.6 (A4), U100.6 (A4)
A5: J1.21, U1.39 (A5), U3.5 (A5), U13.2 (A1), U100.5 (A5)
A6: J1.23, U1.40 (A6), U3.4 (A6), U13.3 (A2), U100.4 (A6)
A7: J1.25, U1.41 (A7), U3.3 (A7), U13.6 (E3), U100.3 (A7)
A8: J1.28, U1.42 (A8), U3.25 (A8), U100.25 (A8)
A9: J1.26, U1.43 (A9), U3.24 (A9), U100.24 (A9)
A10: J1.16, U1.44 (A10), U3.21 (A10)
A11: J1.14, U1.1 (A11), U3.23 (A11)
A12: J1.24, U1.2 (A12), U3.2 (A12)
A13: J1.19, U1.3 (A13), U12.1 (A0)
A14: J1.20, U1.4 (A14), U12.2 (A1)
A15: U1.5 (A15), U12.3 (A2)
Audio_WR: U13.9 (O6); also elsewhere on the board
CPU_CLK: U1.7 (CLK); also elsewhere on the board
CTRL_EN_1: U13.11 (O4); also elsewhere on the board
CTRL_EN_2: U13.15 (O0); also elsewhere on the board
CTRL_R: U13.7 (O7); also elsewhere on the board
D0: J1.5, U1.16 (D0), U3.11 (D0), U100.11 (DQ0); also elsewhere on the board
D1: J1.3, U1.17 (D1), U3.12 (D1), U100.12 (DQ1); also elsewhere on the board
D2: J1.1, U1.14 (D2), U3.13 (D2), U100.13 (DQ2); also elsewhere on the board
D3: J1.4, U1.9 (D3), U3.15 (D3), U100.15 (DQ3); also elsewhere on the board
D4: J1.6, U1.8 (D4), U3.16 (D4), U100.16 (DQ4); also elsewhere on the board
D5: J1.8, U1.10 (D5), U3.17 (D5), U100.17 (DQ5); also elsewhere on the board
D6: J1.10, U1.11 (D6), U3.18 (D6), U100.18 (DQ6); also elsewhere on the board
D7: J1.12, U1.15 (D7), U3.19 (D7), U100.19 (DQ7); also elsewhere on the board
EXT_20_3F: U12.14 (O1)
EXT_40_5F: U12.13 (O2)
EXT_DECODE_STUB: U12.6 (E3); also elsewhere on the board
EXT_IO_STUB: U13.5 (E2); also elsewhere on the board
GND: C1.2, C10.2, C15.2, C16.1, C17.2, C18.1, J1.13, J1.29, U1.33 (GND), U3.1 (VPP), U3.14 (GND), U3.26 (A13), U3.27 (A14), U12.8 (GND), U13.8 (GND), U100.1 (A14), U100.2 (A12), U100.14 (GND), U100.21 (A10), U100.23 (A11), U100.26 (A13); also elsewhere on the board
VCC: C1.1, C10.1, C15.1, C16.2, C17.1, C18.2, J1.30, R1.1, R2.1, R3.1, R44.1, U1.13 (VCC), U3.28 (VCC), U12.16 (VCC), U13.16 (VCC), U100.28 (Vcc); also elsewhere on the board
VDC_R: U13.12 (O3); also elsewhere on the board
VDC_W: U13.13 (O2); also elsewhere on the board

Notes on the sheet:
Revised June 2020: Revised RAM refresh circuit
Revised June 2020: 62256 SRAM
Revised June 2020 - tied /BIOS_OE and /BIOS_CE together for 27C256
Revised October 2021: ~{WAIT} is 2.7k pullup on ChildOfCv schematics
NOTE: I think this GND is actually RF SHIELD GROUND

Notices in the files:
parts and their libraries:
Copyright 2016 Accelerated Designs. All rights reserved.
Copyright 2021 Accelerated Designs. All rights reserved.
